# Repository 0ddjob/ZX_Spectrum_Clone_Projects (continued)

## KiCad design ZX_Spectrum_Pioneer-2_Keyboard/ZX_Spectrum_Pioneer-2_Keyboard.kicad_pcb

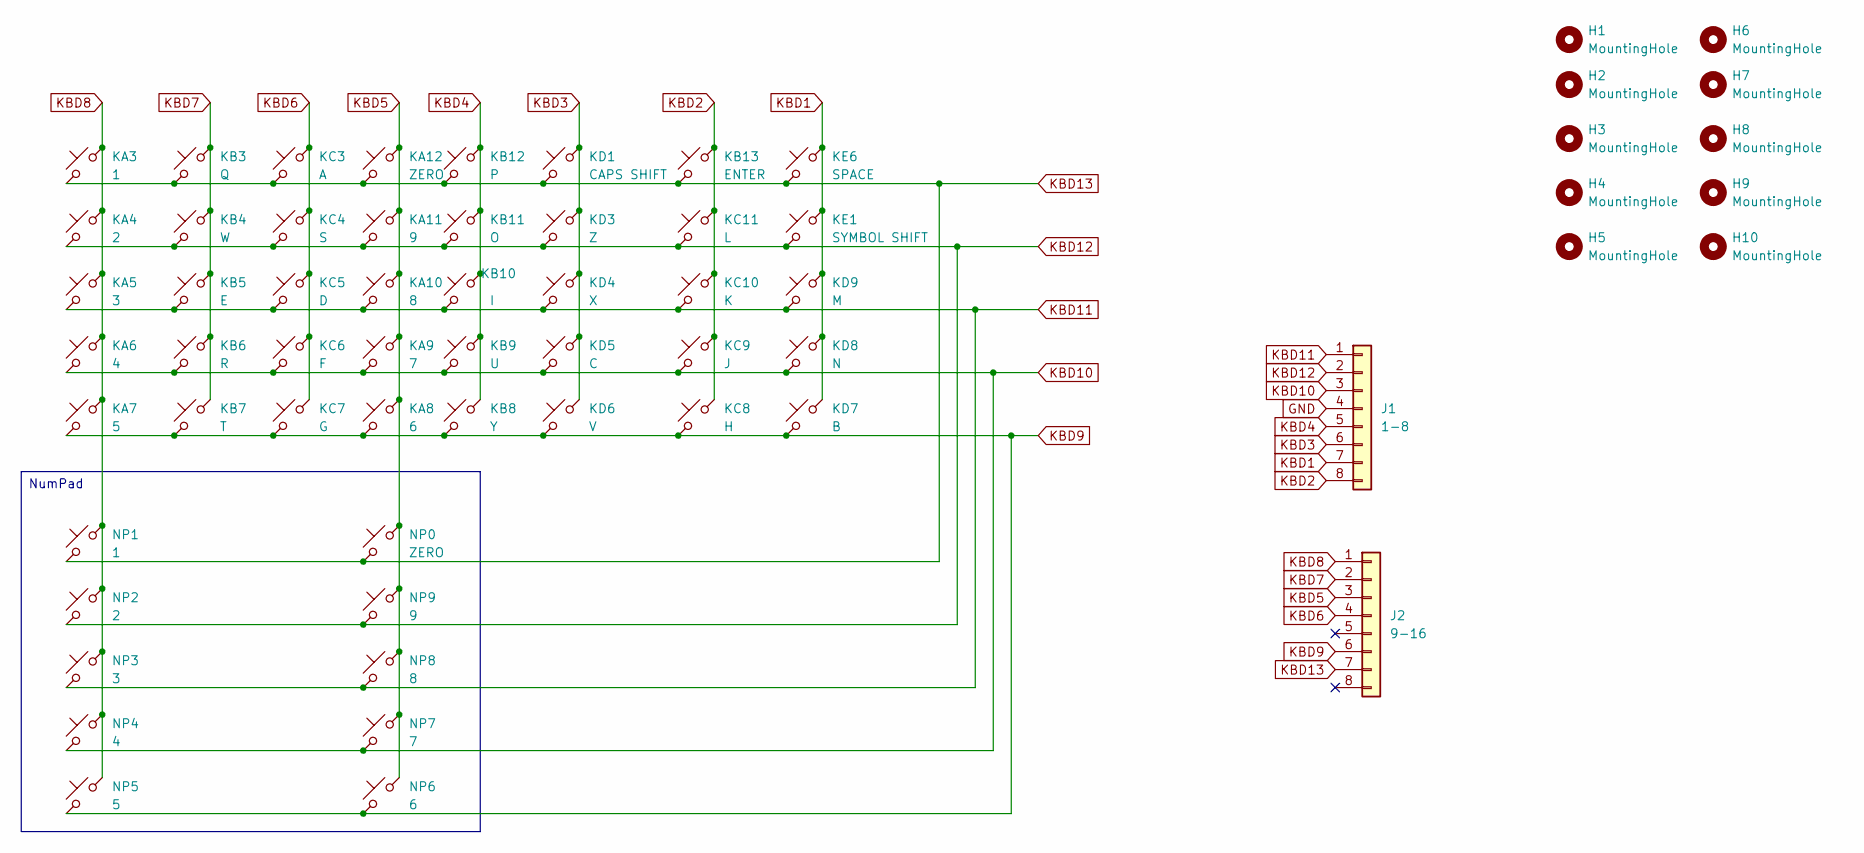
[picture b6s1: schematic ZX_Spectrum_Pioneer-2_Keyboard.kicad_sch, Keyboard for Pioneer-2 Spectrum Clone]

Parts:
H1, H2, H3, H4, H5, H6, H7, H8, H9, H10: MountingHole; MountingHole_3.2mm_M3
J1: 1-8; PinHeader_1x08_P2.54mm_Vertical
J2: 9-16; PinHeader_1x08_P2.54mm_Vertical
KA3: 1; SW_PUSH-12mm
KA4: 2; SW_PUSH-12mm
KA5: 3; SW_PUSH-12mm
KA6: 4; SW_PUSH-12mm
KA7: 5; SW_PUSH-12mm
KA8: 6; SW_PUSH-12mm
KA9: 7; SW_PUSH-12mm
KA10: 8; SW_PUSH-12mm
KA11: 9; SW_PUSH-12mm
KA12: ZERO; SW_PUSH-12mm
KB3: Q; SW_PUSH-12mm
KB4: W; SW_PUSH-12mm
KB5: E; SW_PUSH-12mm
KB6: R; SW_PUSH-12mm
KB7: T; SW_PUSH-12mm
KB8: Y; SW_PUSH-12mm
KB9: U; SW_PUSH-12mm
KB10: I; SW_PUSH-12mm
KB11: O; SW_PUSH-12mm
KB12: P; SW_PUSH-12mm
KB13: ENTER; SW_PUSH-12mm
KC3: A; SW_PUSH-12mm
KC4: S; SW_PUSH-12mm
KC5: D; SW_PUSH-12mm
KC6: F; SW_PUSH-12mm
KC7: G; SW_PUSH-12mm
KC8: H; SW_PUSH-12mm
KC9: J; SW_PUSH-12mm
KC10: K; SW_PUSH-12mm
KC11: L; SW_PUSH-12mm
KD1: CAPS SHIFT; SW_PUSH-12mm
KD3: Z; SW_PUSH-12mm
KD4: X; SW_PUSH-12mm
KD5: C; SW_PUSH-12mm
KD6: V; SW_PUSH-12mm
KD7: B; SW_PUSH-12mm
KD8: N; SW_PUSH-12mm
KD9: M; SW_PUSH-12mm
KE1: SYMBOL SHIFT; SW_PUSH-12mm
KE6: SPACE; SW_PUSH-12mm
NP0: ZERO; SW_PUSH-12mm
NP1: 1; SW_PUSH-12mm
NP2: 2; SW_PUSH-12mm
NP3: 3; SW_PUSH-12mm
NP4: 4; SW_PUSH-12mm
NP5: 5; SW_PUSH-12mm
NP6: 6; SW_PUSH-12mm
NP7: 7; SW_PUSH-12mm
NP8: 8; SW_PUSH-12mm
NP9: 9; SW_PUSH-12mm

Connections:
GND: J1.4
KBD1: J1.7, KD7.2, KD8.2, KD9.2, KE1.2, KE6.2
KBD2: J1.8, KB13.2, KC8.2, KC9.2, KC10.2, KC11.2
KBD3: J1.6, KD1.2, KD3.2, KD4.2, KD5.2, KD6.2
KBD4: J1.5, KB8.2, KB9.2, KB10.2, KB11.2, KB12.2
KBD5: J2.3, KA8.2, KA9.2, KA10.2, KA11.2, KA12.2, NP0.2, NP6.2, NP7.2, NP8.2, NP9.2
KBD6: J2.4, KC3.2, KC4.2, KC5.2, KC6.2, KC7.2
KBD7: J2.2, KB3.2, KB4.2, KB5.2, KB6.2, KB7.2
KBD8: J2.1, KA3.2, KA4.2, KA5.2, KA6.2, KA7.2, NP1.2, NP2.2, NP3.2, NP4.2, NP5.2
KBD9: J2.6, KA7.1, KA8.1, KB7.1, KB8.1, KC7.1, KC8.1, KD6.1, KD7.1, NP5.1, NP6.1
KBD10: J1.3, KA6.1, KA9.1, KB6.1, KB9.1, KC6.1, KC9.1, KD5.1, KD8.1, NP4.1, NP7.1
KBD11: J1.1, KA5.1, KA10.1, KB5.1, KB10.1, KC5.1, KC10.1, KD4.1, KD9.1, NP3.1, NP8.1
KBD12: J1.2, KA4.1, KA11.1, KB4.1, KB11.1, KC4.1, KC11.1, KD3.1, KE1.1, NP2.1, NP9.1
KBD13: J2.7, KA3.1, KA12.1, KB3.1, KB12.1, KB13.1, KC3.1, KD1.1, KE6.1, NP0.1, NP1.1

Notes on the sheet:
NumPad

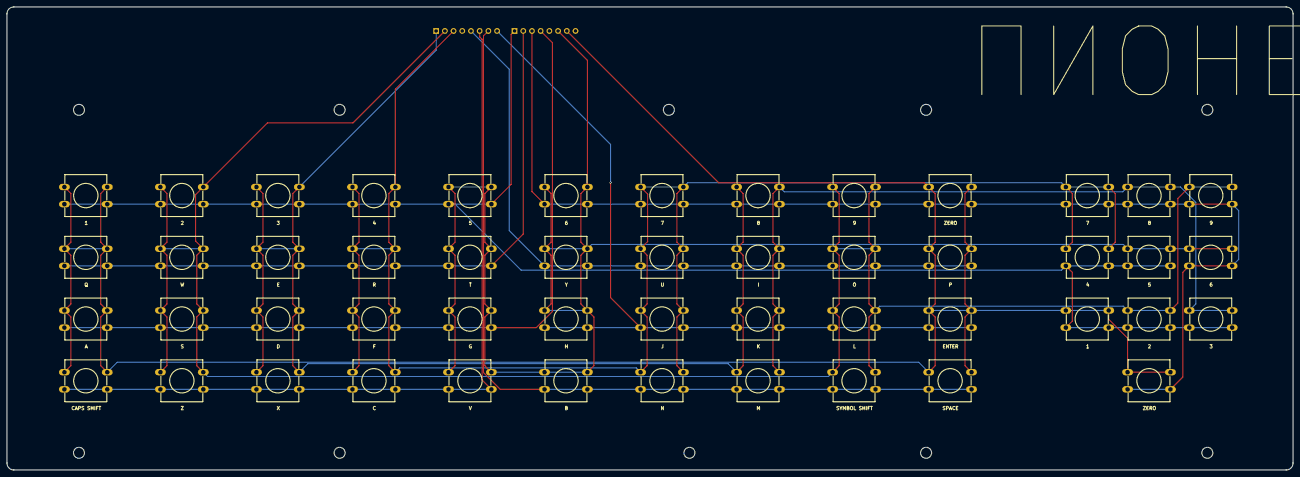
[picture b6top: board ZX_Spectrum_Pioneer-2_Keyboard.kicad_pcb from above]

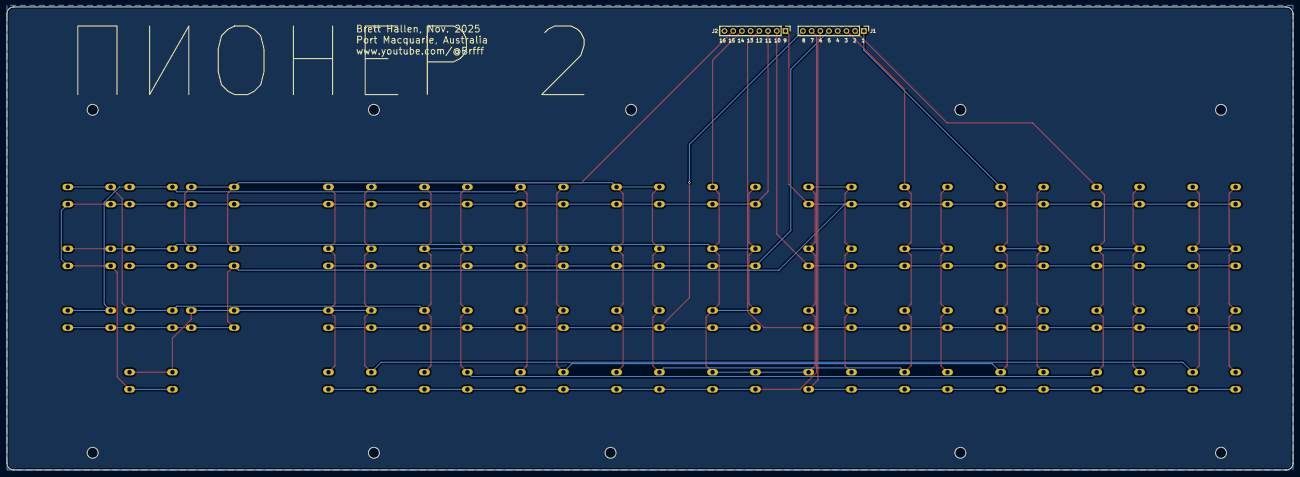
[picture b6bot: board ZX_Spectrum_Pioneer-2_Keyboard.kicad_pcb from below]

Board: 2 copper layers, 375.0 x 135.0 mm, 62 parts (2 on the bottom side), 13 nets.

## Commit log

2025-11-16 Added files
2025-11-16 Added Leningrad-2 symbol & footprint
2025-11-16 PCB changes
2025-11-16 Updated Leningrad-2 symbol
2025-11-16 Added ~IORQGE signal
    Thanks to Oleh S. suggestion on UCHC "Ukrainian Computing History Community"
2025-11-17 Reorganise folders
2025-11-17 Added ~IORQGR signal
2025-11-17 Moved from Sinclair repository
2025-11-17 PCB updates
2025-11-20 Moved to own folder
2025-11-20 Moved from own repository
2025-11-20 Corrected PCB text layer
